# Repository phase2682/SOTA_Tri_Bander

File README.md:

# SOTA_Tri_Bander
Modifications to Tri-Bander CW transceiver to make it more SOTA friendly 
The schematic, code, layout files for https://www.ai6xg.com/post/kd1jv_tri_bander_sota-friendly

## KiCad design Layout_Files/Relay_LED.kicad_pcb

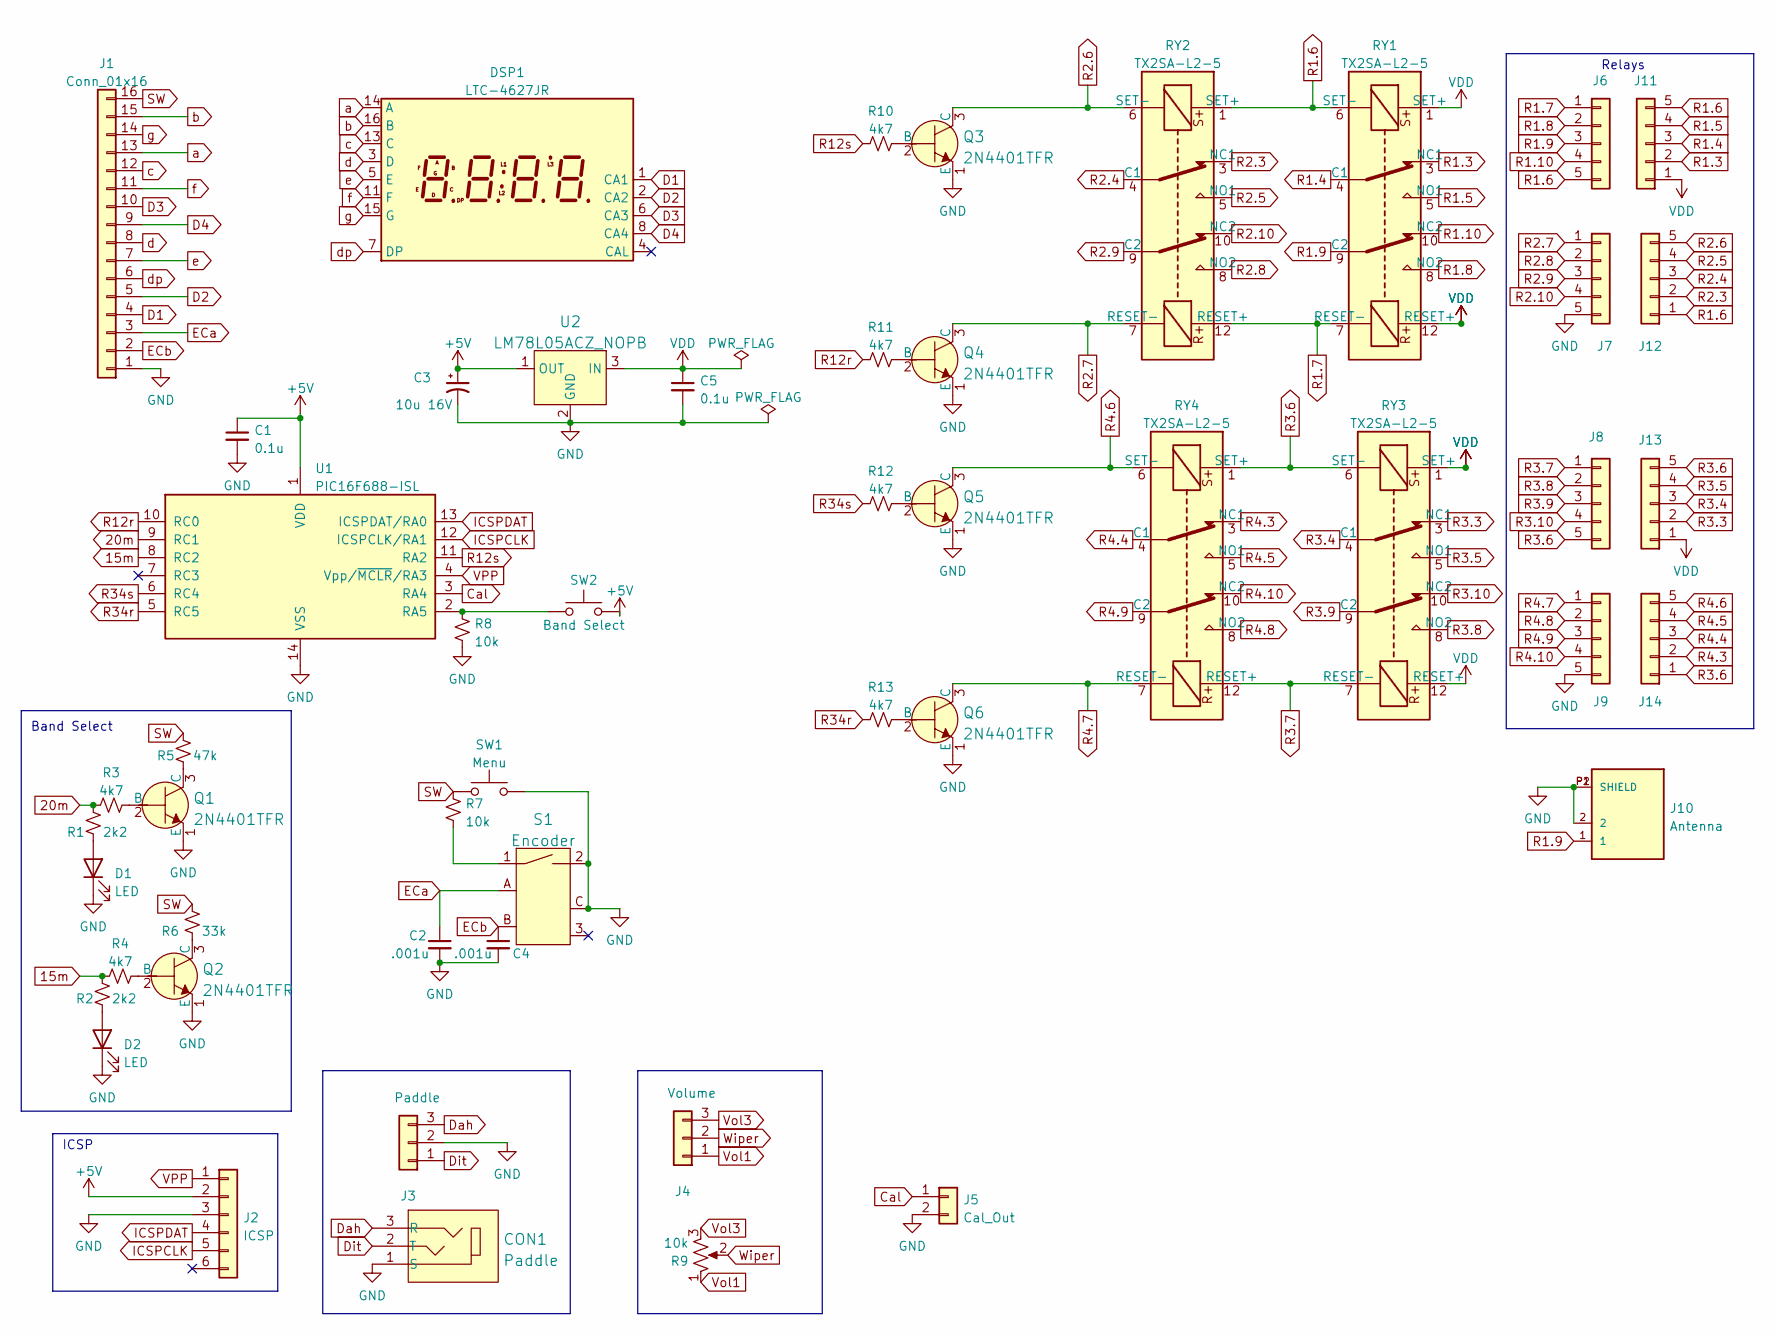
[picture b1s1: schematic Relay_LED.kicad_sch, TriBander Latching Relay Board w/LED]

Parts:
C1, C5: 0.1u; C_Rect_L4.0mm_W2.5mm_P2.50mm
C2, C4: .001u; C_Disc_D3.4mm_W2.1mm_P2.50mm
C3: 10u 16V; CP_Radial_D6.3mm_P2.50mm
CON1: Paddle; CUI_SJ1-3513N round pin; MPN SJ1-3523N; Digi-Key_PN CP1-3523N-ND
D1, D2: LED; LED_D3.0mm
DSP1: LTC-4627JR; LTC-4627Jx
J1: Conn_01x16; PinHeader_1x16_P2.54mm_Vertical
J2: ICSP; PinHeader_1x06_P2.54mm_Vertical
J3: Paddle; PinHeader_1x03_P2.54mm_Vertical
J4: Volume; PinHeader_1x03_P2.54mm_Vertical
J5: Cal_Out; PinHeader_1x02_P2.54mm_Vertical
J6, J7, J8, J9, J11, J12, J13, J14: Conn_01x05; PinHeader_1x05_P2.54mm_Vertical
J10: Antenna; CONN_1-1337543-0
Q1, Q2, Q3, Q4, Q5, Q6: 2N4401TFR; TO-92-3_Formed_Leads; MPN 2N4401TFR; Digi-Key_PN 2N4401D26ZCT-ND
R1, R2: 2k2; R THT .25W minP
R3, R4, R10, R11, R12, R13: 4k7; R THT .25W minP
R5: 47k; R THT .25W minP
R6: 33k; R THT .25W minP
R7, R8: 10k; R THT .25W minP
R9: 10k; Potentiometer_Bourns_PTV09A-1_Single_Vertical
RY1, RY2, RY3, RY4: TX2SA-L2-5; Relay_DPDT_Kemet_EE2_NU_DoubleCoil
S1: Encoder; Rotary_Encoder_Switched_PEC11R; MPN PEC11R-4215F-S0024; Digi-Key_PN PEC11R-4215F-S0024-ND
SW1: Menu; SW_PUSH_6mm
SW2: Band Select; SW_PUSH_6mm
U1: PIC16F688-ISL; SOIC-14_3.9x8.7mm_P1.27mm
U2: LM78L05ACZ_NOPB; TO-92-3; MPN LM78L05ACZ/NOPB; Digi-Key_PN LM78L05ACZNS/NOPB-ND

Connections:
15m: R2.2, R4.1, U1.8 (RC2)
20m: R1.2, R3.1, U1.9 (RC1)
+5V: C1.1, C3.1, J2.2, SW2.2, U1.1 (VDD), U2.1 (OUT)
Cal: J5.1, U1.3 (RA4)
D1: DSP1.1 (CA1), J1.4
D2: DSP1.2 (CA2), J1.5
D3: DSP1.6 (CA3), J1.10
D4: DSP1.8 (CA4), J1.9
Dah: CON1.3 (R), J3.3
Dit: CON1.2 (T), J3.1
ECa: C2.1, J1.3, S1.A (CH_A)
ECb: C4.1, J1.2, S1.B (CH_B)
GND: C1.2, C2.2, C3.2, C4.2, C5.2, CON1.1 (S), D1.1 (K), D2.1 (K), J1.1, J2.3, J3.2, J5.2, J7.5, J9.5, J10.2, J10.P1 (SHIELD), J10.P2 (SHIELD), Q1.1 (E), Q2.1 (E), Q3.1 (E), Q4.1 (E), Q5.1 (E), Q6.1 (E), R8.1, S1.2, S1.C (COM), SW1.2, U1.14 (VSS), U2.2 (GND)
ICSPCLK: J2.5, U1.12 (ICSPCLK/RA1)
ICSPDAT: J2.4, U1.13 (ICSPDAT/RA0)
unnamed: D1.2 (A), R1.1
unnamed: D2.2 (A), R2.1
unnamed: Q1.2 (B), R3.2
unnamed: Q1.3 (C), R5.2
unnamed: Q2.2 (B), R4.2
unnamed: Q2.3 (C), R6.2
unnamed: Q3.2 (B), R10.2
unnamed: Q4.2 (B), R11.2
unnamed: Q5.2 (B), R12.2
unnamed: Q6.2 (B), R13.2
unnamed: R7.2, S1.1
unnamed: R8.2, SW2.1, U1.2 (RA5)
R1.3: J11.2, RY1.3 (NC1)
R1.4: J11.3, RY1.4 (C1)
R1.5: J11.4, RY1.5 (NO1)
R1.6: J6.5, J11.5, J12.1, RY1.6 (SET-), RY2.1 (SET+)
R1.7: J6.1, RY1.7 (RESET-), RY2.12 (RESET+)
R1.8: J6.2, RY1.8 (NO2)
R1.9: J6.3, J10.1, RY1.9 (C2)
R1.10: J6.4, RY1.10 (NC2)
R2.3: J12.2, RY2.3 (NC1)
R2.4: J12.3, RY2.4 (C1)
R2.5: J12.4, RY2.5 (NO1)
R2.6: J12.5, Q3.3 (C), RY2.6 (SET-)
R2.7: J7.1, Q4.3 (C), RY2.7 (RESET-)
R2.8: J7.2, RY2.8 (NO2)
R2.9: J7.3, RY2.9 (C2)
R2.10: J7.4, RY2.10 (NC2)
R3.3: J13.2, RY3.3 (NC1)
R3.4: J13.3, RY3.4 (C1)
R3.5: J13.4, RY3.5 (NO1)
R3.6: J8.5, J13.5, J14.1, RY3.6 (SET-), RY4.1 (SET+)
R3.7: J8.1, RY3.7 (RESET-), RY4.12 (RESET+)
R3.8: J8.2, RY3.8 (NO2)
R3.9: J8.3, RY3.9 (C2)
R3.10: J8.4, RY3.10 (NC2)
R4.3: J14.2, RY4.3 (NC1)
R4.4: J14.3, RY4.4 (C1)
R4.5: J14.4, RY4.5 (NO1)
R4.6: J14.5, Q5.3 (C), RY4.6 (SET-)
R4.7: J9.1, Q6.3 (C), RY4.7 (RESET-)
R4.8: J9.2, RY4.8 (NO2)
R4.9: J9.3, RY4.9 (C2)
R4.10: J9.4, RY4.10 (NC2)
R12r: R11.1, U1.10 (RC0)
R12s: R10.1, U1.11 (RA2)
R34r: R13.1, U1.5 (RC5)
R34s: R12.1, U1.6 (RC4)
SW: J1.16, R5.1, R6.1, R7.1, SW1.1
VDD: C5.1, J11.1, J13.1, RY1.1 (SET+), RY1.12 (RESET+), RY3.1 (SET+), RY3.12 (RESET+), U2.3 (IN)
VPP: J2.1, U1.4 (Vpp/~MCLR/RA3)
Vol1: J4.1, R9.1
Vol3: J4.3, R9.3
Wiper: J4.2, R9.2
a: DSP1.14 (A), J1.13
b: DSP1.16 (B), J1.15
c: DSP1.13 (C), J1.12
d: DSP1.3 (D), J1.8
dp: DSP1.7 (DP), J1.6
e: DSP1.5 (E), J1.7
f: DSP1.11 (F), J1.11
g: DSP1.15 (G), J1.14

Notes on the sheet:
Relays
Band Select
ICSP

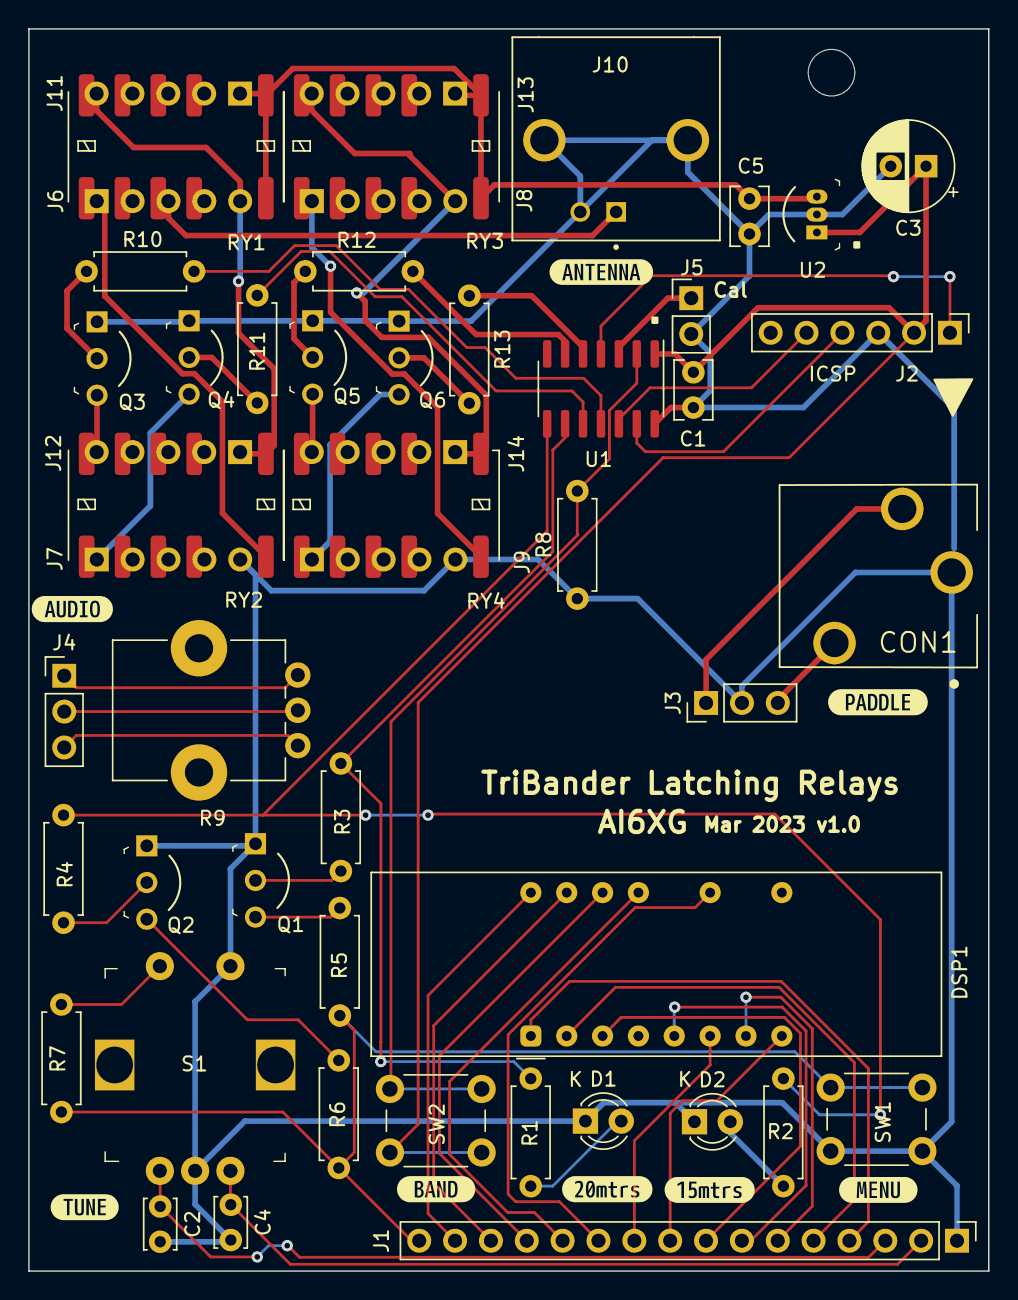
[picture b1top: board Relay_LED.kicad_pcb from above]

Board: 2 copper layers, 68.0 x 88.0 mm, 59 parts (0 on the bottom side), 77 nets.

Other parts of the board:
kibuzzard-6406D9A6: G***; kibuzzard-6406D9A6
kibuzzard-6406D9EC: G***; kibuzzard-6406D9EC
kibuzzard-6406DA0A: G***; kibuzzard-6406DA0A
kibuzzard-6406DC2D: G***; kibuzzard-6406DC2D
kibuzzard-6406DC4B: G***; kibuzzard-6406DC4B
kibuzzard-6406DC57: G***; kibuzzard-6406DC57
kibuzzard-6406DC87: G***; kibuzzard-6406DC87
kibuzzard-6407CA45: G***; kibuzzard-6407CA45

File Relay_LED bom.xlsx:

Source: | C:\Users\Dan Koellen AI6XG\OneDrive\QRP Kits\Relay Board\Relay_LED\Relay_LED.ki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
Date: | 7/4/2023 6:56:38 PM
Tool: | Eeschema (6.0.7)
Component Count: | 51
Ref | Value | Footprint
C1 | 0.1u | Capacitor_THT:C_Rect_L4.0mm_W2.5mm_P2.50mm
C2 | .001u | Capacitor_THT:C_Disc_D3.4mm_W2.1mm_P2.50mm
C3 | 10u 16V | Capacitor_THT:CP_Radial_D6.3mm_P2.50mm
C4 | .001u | Capacitor_THT:C_Disc_D3.4mm_W2.1mm_P2.50mm
C5 | 0.1u | Capacitor_THT:C_Rect_L4.0mm_W2.5mm_P2.50mm
CON1 | Paddle | CUI_SJ1-3523:CUI_SJ1-3513N round pin
D1 | LED | LED_THT:LED_D3.0mm
D2 | LED | LED_THT:LED_D3.0mm
DSP1 | LTC-4627JR | Display_7Segment:LTC-4627Jx
J1 | Conn_01x16 | Connector_PinHeader_2.54mm:PinHeader_1x16_P2.54mm_Vertical
J2 | ICSP | Connector_PinHeader_2.54mm:PinHeader_1x06_P2.54mm_Vertical
J3 | Paddle | Connector_PinHeader_2.54mm:PinHeader_1x03_P2.54mm_Vertical
J4 | Volume | Connector_PinHeader_2.54mm:PinHeader_1x03_P2.54mm_Vertical
J5 | Cal_Out | Connector_PinHeader_2.54mm:PinHeader_1x02_P2.54mm_Vertical
J6 | Conn_01x05 | Connector_PinHeader_2.54mm:PinHeader_1x05_P2.54mm_Vertical
J7 | Conn_01x05 | Connector_PinHeader_2.54mm:PinHeader_1x05_P2.54mm_Vertical
J8 | Conn_01x05 | Connector_PinHeader_2.54mm:PinHeader_1x05_P2.54mm_Vertical
J9 | Conn_01x05 | Connector_PinHeader_2.54mm:PinHeader_1x05_P2.54mm_Vertical
J10 | Antenna | AI6XG:CONN_1-1337543-0
J11 | Conn_01x05 | Connector_PinHeader_2.54mm:PinHeader_1x05_P2.54mm_Vertical
J12 | Conn_01x05 | Connector_PinHeader_2.54mm:PinHeader_1x05_P2.54mm_Vertical
J13 | Conn_01x05 | Connector_PinHeader_2.54mm:PinHeader_1x05_P2.54mm_Vertical
J14 | Conn_01x05 | Connector_PinHeader_2.54mm:PinHeader_1x05_P2.54mm_Vertical
Q1 | 2N4401TFR | digikey-footprints:TO-92-3_Formed_Leads
Q2 | 2N4401TFR | digikey-footprints:TO-92-3_Formed_Leads
Q3 | 2N4401TFR | digikey-footprints:TO-92-3_Formed_Leads
Q4 | 2N4401TFR | digikey-footprints:TO-92-3_Formed_Leads
Q5 | 2N4401TFR | digikey-footprints:TO-92-3_Formed_Leads
Q6 | 2N4401TFR | digikey-footprints:TO-92-3_Formed_Leads
R1 | 2k2 | AI6XG:R THT .25W minP
R2 | 2k2 | AI6XG:R THT .25W minP
R3 | 4k7 | AI6XG:R THT .25W minP
R4 | 4k7 | AI6XG:R THT .25W minP
R5 | 47k | AI6XG:R THT .25W minP
R6 | 33k | AI6XG:R THT .25W minP
R7 | 10k | AI6XG:R THT .25W minP
R8 | 10k | AI6XG:R THT .25W minP
R9 | 10k | Potentiometer_THT:Potentiometer_Bourns_PTV09A-1_Single_Vertical
R10 | 4k7 | AI6XG:R THT .25W minP
R11 | 4k7 | AI6XG:R THT .25W minP
R12 | 4k7 | AI6XG:R THT .25W minP
R13 | 4k7 | AI6XG:R THT .25W minP
RY1 | TX2SA-L2-5 | Relay_SMD:Relay_DPDT_Kemet_EE2_NU_DoubleCoil
RY2 | TX2SA-L2-5 | Relay_SMD:Relay_DPDT_Kemet_EE2_NU_DoubleCoil
RY3 | TX2SA-L2-5 | Relay_SMD:Relay_DPDT_Kemet_EE2_NU_DoubleCoil
RY4 | TX2SA-L2-5 | Relay_SMD:Relay_DPDT_Kemet_EE2_NU_DoubleCoil
S1 | Encoder | digikey-footprints:Rotary_Encoder_Switched_PEC11R
SW1 | Menu | Button_Switch_THT:SW_PUSH_6mm
SW2 | Band Select | Button_Switch_THT:SW_PUSH_6mm
U1 | PIC16F688-ISL | Package_SO:SOIC-14_3.9x8.7mm_P1.27mm
U2 | LM78L05ACZ_NOPB | digikey-footprints:TO-92-3

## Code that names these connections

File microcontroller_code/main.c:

/*
 * File:   main.c
 * Author: Dan Koellen AI6XG
 *
 * Creation started on February 9, 2023, 5:18 PM
 */

/*
*  Project:                      Relay proto                      *
*                                                                             *
*  Description: This file contains C code for a PIC16F688 using xc8 version
*  compiler.
*  This is the interface to select the proper latching relay configuration  
 *  for 40, 20 and 15 meters on the QRPkits Tribander.  the band will be 
 * selected by successive button pushes to step through the bands
 * Two outputs will drive transistors that will be open collector to 
 * ground the appropriate band selecting resistor
 * 
 * Latching relays are being used instead of the monostable relays of the
 * original design.  A pulsed output will drive transistors that will set or 
 * reset the latching relays to the Tribander main board.
 * 
 * RA0, RA1 and RA3 are reserved for ICSP

	In debug mode:
	

	in non- debug 				
				
				

				
				

				

				
*  Versions:                                                                  *
*                                                                             *
*  MAJ.MIN - AUTHOR - CHANGE DESCRIPTION                                      *
*                                                                             *
*   1.0    - 
*
*   2.0    -                                                                  *
******************************************************************************/



#include <xc.h>
#include "configBits.h"
#include <stdio.h>
#include <stdlib.h>

#define band_set	RA5                 //set input to advance band 
#define _15_mtr     RC2                 //15 meters band set output
#define _20_mtr     RC1                 //20 meters band set output

#define R12s        RA2                 //relays 1 and 2 set output
#define R12r        RC0                 //relays 1 and 2 reset output
#define R34s        RC4                 //relays 3 and 4 set output
#define R34r        RC5                 //relays 3 and 4 reset output
#define relay_pulse_dur 3               //relay pulse duration mSecs output
                            
#define timer_reset_value 	9			//reset value for timer0
#define cal_out     RA4                 //cal output F = 1/(2*timer_events) output

//function declaration for clearing flag after duration mSecs
unsigned char 	DurationClear(unsigned char start, unsigned char duration, unsigned char reset, unsigned char events);

unsigned char 	timer_events = 0;			//number of timer0 overflows
unsigned char 	previous_timer_event =0;	//previous timer_events

unsigned char 	band = 0;            	//0->40 mtrs, 1->20 mtrs, 2->15 mtrs
unsigned char 	previous_band = 3;		//forces band <> previous_band at startup
unsigned int 	state = 0;				//debounce state holder

unsigned char   R12s_time = 0;          //time that R12 is set
unsigned char   R12r_time = 0;          //time that R12 is reset
unsigned char   R34s_time = 0;          //time that R34 is set
unsigned char   R34r_time = 0;          //time that R34 is reset



void main(void) {

PORTA = PORTC= 0;						//Clear PortA and C
TRISA = 0b0100000;						//Ports A5 input, A0,1,2,3,4 outputs,
TRISC = 0; 								//All PortC is output
CMCON0 = 0b111;                         //Comparator Off
CMCON1 = 0b10;
ANSEL = 0b00000000;						//All digital 

//Interrupt setup
GIE = 1;								//global interrupt enable
INTF = 0;								//clear the external interrupt flag
INTE = 0;								//disable0/enable1 external interrupt on RA2

//setup Timer0
OPTION_REGbits.PSA = 0;					//prescaler for T0
OPTION_REGbits.PS = 0b001;              //prescaler set to 1:4
T0CS = 0;								//Fosc/4 timer
T0IE = 1;                               //T0 interrupt enabled 

while(1==1){
   
//millisecond tasks
if(timer_events != previous_timer_event)	//test state every tmr0 interrupt
	{
	//debounce  band_set -> increment band for each press
        state = ((state << 1) | (!band_set) | 0xE000);	//must be clear after 12 loops
		if (state == 0xF000)                            //true if band_set clear
			{
			band++;							//increment band to next band
			if (band > 2) band = 0;         //go back to initial band
            
        }
             cal_out ^= 1;                  //toggle cal_out
        
	previous_timer_event = timer_events;

    if (band != previous_band)              //test if the band has changed
    {
        if (band == 0) 					//40 meters
        {
            _15_mtr = 0;                //band set
            _20_mtr = 0;                //band set

            R12r = 1;                   //reset relays 1 and 2
            R34r = 1;                   //reset relays 3 and 4
            R12r_time = R34r_time = timer_events;
                                        //time relay pulse starts

        }								//end 40 meters if

        if (band == 1)					//20 meters	
            {

            _15_mtr = 0;                //band set
            _20_mtr = 1;                //band set

            R12r = 1;                   //reset relays 1 and 2
            R34s = 1;                   //set relays 3 and 4
            R12r_time = R34s_time = timer_events;
                                        //time relay pulse starts

            }                           //end 20 meters if

        if (band  == 2)					//15 meters
            {

            _15_mtr = 1;                //band set
            _20_mtr = 0;                //band set

            R12s = 1;                   //set relays 1 and 2
     
            R12s_time = timer_events;   //time relay pulse starts


            }							//end 15 meters if
        previous_band = band;
        }                               //end previous_band if
    
    }                                   //end timer_events if

//clear relay pulse after relay_pulse_dur duration
 R12r &= DurationClear(R12r_time, relay_pulse_dur, 255, timer_events ) ;
 R34r &= DurationClear(R34r_time, relay_pulse_dur, 255, timer_events ) ;
 R12s &= DurationClear(R12s_time, relay_pulse_dur, 255, timer_events ) ;
 R34s &= DurationClear(R34s_time, relay_pulse_dur, 255, timer_events ) ;
    
}                                   //end while(1==1)
    
    
}                                  //end main(void)

/**********************************************************************************************
		Function Name: 	unsigned char DurationClear(unsigned char start, unsigned char duration, 
 *                                                  unsigned char reset, unsigned char events)
		Return Value:	flag = 0
		Parmeters:		start is when flag was set, duration is mSecs flag to be set for,
 *                      reset is number of timer_events when reset or overflowed (usigned char-->255), 
 *                      events is timer_events count
		Description:	returns 0 after duration mSecs, otherwise 1
	
	************************************************************************************************/
unsigned char DurationClear(unsigned char start, unsigned char duration, unsigned char reset, unsigned char events)
{
unsigned char flag = 1;
unsigned char time_now1 = events;						//current total of timer overflows
unsigned char delta = reset - duration;                 //region where overflow will occur during duration
if (start >= delta & time_now1 >= delta)
                                        ;				//do nothing until time_now1 is overflowed	
if (start >= delta & time_now1 < delta) 				//adapt for overflow reset
	{
	if ((time_now1 - start + reset)>=duration) flag = 0;	//clear flag at the end of duration
	}													//end if
if (start < delta)                                      //no adapting outside of overflow region
	{
	if (time_now1 - start >= duration) flag = 0;			//clear  flag
	}													//end if
return flag;
}														//end function




void __interrupt()
isr(void)
{
		
	if (T0IF)
		{
			timer_events++;						//increment number of T0 overflow
			TMR0 = timer_reset_value;			//reload starting value in T0
			T0IF = 0;							//clear interrupt flag
		}										//end T0IF if
}

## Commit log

2023-07-17 Create Layout
2023-07-18 Create test
2024-05-06 Update README.md
    corrected link to post
